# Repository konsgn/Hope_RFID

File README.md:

HOPE RFID reader.

By:Konstantin

Scans EM tags using a ATMEGA32u4.
Has usb for computer connection
Has nrf24l01+ section for wireless, 2 headers allow use of existing sparkfun breakout / HOPE 8 Badge.
Has 2-line LCD display
Has 2 LED's and buzzer tied to reader module.

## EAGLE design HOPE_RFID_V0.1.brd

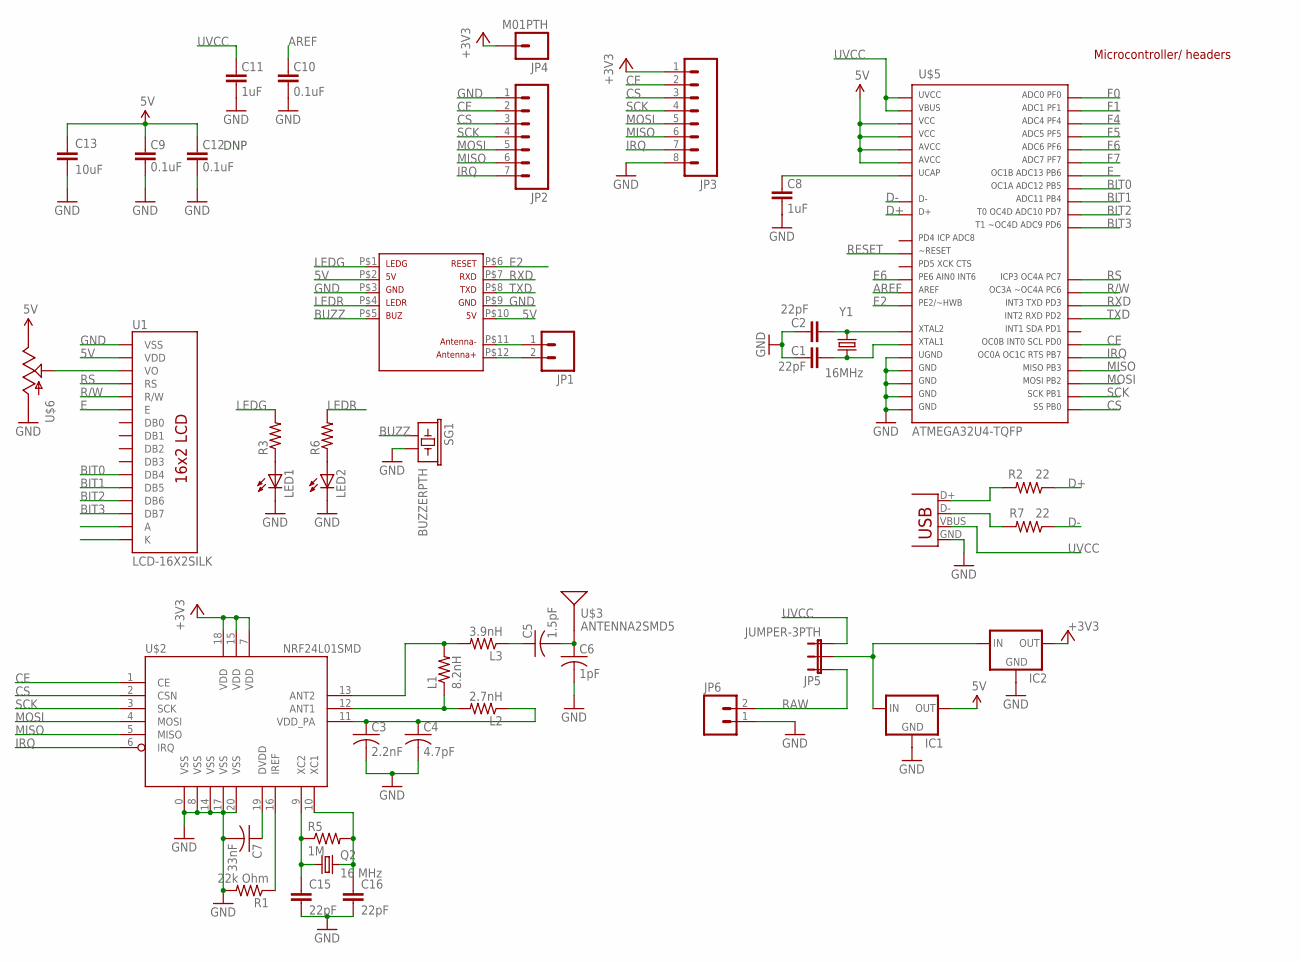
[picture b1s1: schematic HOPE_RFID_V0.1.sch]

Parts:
C1, C2: 22pF; 0805
C3: 2.2nF; C0402
C4: 4.7pF; C0402
C5: 1.5pF; C0402
C6: 1pF; C0402
C7: 33nF; C0402
C8, C11: 1uF; 0603-CAP
C9, C10, C12: 0.1uF; 0603-CAP
C13: 10uF; C2012
C15, C16: 22pF; 0603-CAP
IC1, IC2: V_REG_78XXSIDE; 78XXL
JP1: M02PTH; 1X02
JP2: M07; 1X07
JP3: M081X08; 1X08
JP4: M01PTH; 1X01
JP5: JUMPER-3PTH; 1X03
JP6: M023.5MM; SCREWTERMINAL-3.5MM-2
L1: 8.2nH; R0402
L2: 2.7nH; R0402
L3: 3.9nH; R0402
LED1, LED2: LED5MM
Q2: 16 MHz; CRYSTAL-SMD-5X3
R1: 22k Ohm; R0805
R2, R7: 22; 0805
R3, R6: RESISTORAXIAL-0.3; AXIAL-0.3
R5: 1M; R0805
SG1: BUZZERPTH; BUZZER-12MM
U1: LCD-16X2SILK; LCD-16X2
U$1: RDM880
U$2: NRF24L01SMD; QFN20
U$3: ANTENNA2SMD5; ANTENNA-CHIP5
U$5: ATMEGA32U4-TQFP; TQFP44
U$6: POTTRIM; TRIM_POT
X1: USB; USB-MINIB-NOHOLE
Y1: 16MHz; ABM2-8X4.5-CRYSTAL

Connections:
5V: C9.2, C12.2, C13.1, IC1.OUT, U1.2 (VDD), U$1.P$2, U$1.P$10, U$5.14, U$5.24, U$5.34, U$5.44, U$6.2 (E)
+3V3: IC2.OUT, JP3.1, JP4.1, U$2.7 (VDD), U$2.15 (VDD), U$2.18 (VDD)
AREF: C10.2, U$5.42
BIT0: U1.11 (DB4), U$5.29
BIT1: U1.12 (DB5), U$5.28
BIT2: U1.13 (DB6), U$5.27
BIT3: U1.14 (DB7), U$5.26
BUZZ: SG1.+ (1), U$1.P$5
CE: JP2.2, JP3.2, U$2.1 (CE), U$5.18
CS: JP2.3, JP3.3, U$2.2 (CSN), U$5.8
D+: R2.1, U$5.4
D-: R7.1, U$5.3
E: U1.6 (E), U$5.30
E2: U$1.P$6, U$5.33
E6: U$5.1
F0: U$5.41
F1: U$5.40
F4: U$5.39
F5: U$5.38
F6: U$5.37
F7: U$5.36
GND: C1.2, C2.2, C3.2, C4.2, C6.2, C7.2, C8.1, C9.1, C10.1, C11.1, C12.1, C13.2, C15.2, C16.2, IC1.GND, IC2.GND, JP2.1, JP3.8, JP6.1, LED1.K (C), LED2.K (C), R1.2, SG1.- (2), U1.1 (VSS), U$1.P$3, U$1.P$9, U$2.0 (VSS), U$2.8 (VSS), U$2.14 (VSS), U$2.17 (VSS), U$2.20 (VSS), U$5.5, U$5.15, U$5.23, U$5.35, U$5.43, U$6.3 (A), X1.GND
IRQ: JP2.7, JP3.7, U$2.6 (IRQ), U$5.12
LEDG: R3.P$2 (2), U$1.P$1
LEDR: R6.P$2 (2), U$1.P$4
MISO: JP2.6, JP3.6, U$2.5 (MISO), U$5.11
MOSI: JP2.5, JP3.5, U$2.4 (MOSI), U$5.10
unnamed: JP1.1, U$1.P$11
unnamed: JP1.2, U$1.P$12
unnamed: C15.1, Q2.1, R5.1, U$2.9 (XC2)
unnamed: C1.1, U$5.16, Y1.P$1 (1)
unnamed: C3.1, C4.1, L2.1, U$2.11 (VDD_PA)
unnamed: L1.1, L2.2, U$2.12 (ANT1)
unnamed: L1.2, L3.2, U$2.13 (ANT2)
unnamed: C5.1, L3.1
unnamed: C5.2, C6.1, U$3.FEED
unnamed: C2.1, U$5.17, Y1.P$2 (2)
unnamed: IC1.IN, IC2.IN, JP5.2
unnamed: C7.1, U$2.19 (DVDD)
unnamed: R1.1, U$2.16 (IREF)
unnamed: C8.2, U$5.6
unnamed: R7.2, X1.D-
unnamed: R2.2, X1.D+
unnamed: LED1.A, R3.P$1 (1)
unnamed: LED2.A, R6.P$1 (1)
unnamed: U1.3 (VO), U$6.1 (S)
unnamed: C16.1, Q2.3 (2), R5.2, U$2.10 (XC1)
R/W: U1.5 (R/W), U$5.31
RAW: JP5.1, JP6.2
RESET: U$5.13
RS: U1.4 (RS), U$5.32
RXD: U$1.P$7, U$5.21
SCK: JP2.4, JP3.4, U$2.3 (SCK), U$5.9
TXD: U$1.P$8, U$5.20
UVCC: C11.2, JP5.3, U$5.2, U$5.7, X1.VBUS

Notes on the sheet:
Microcontroller/ headers
DNP

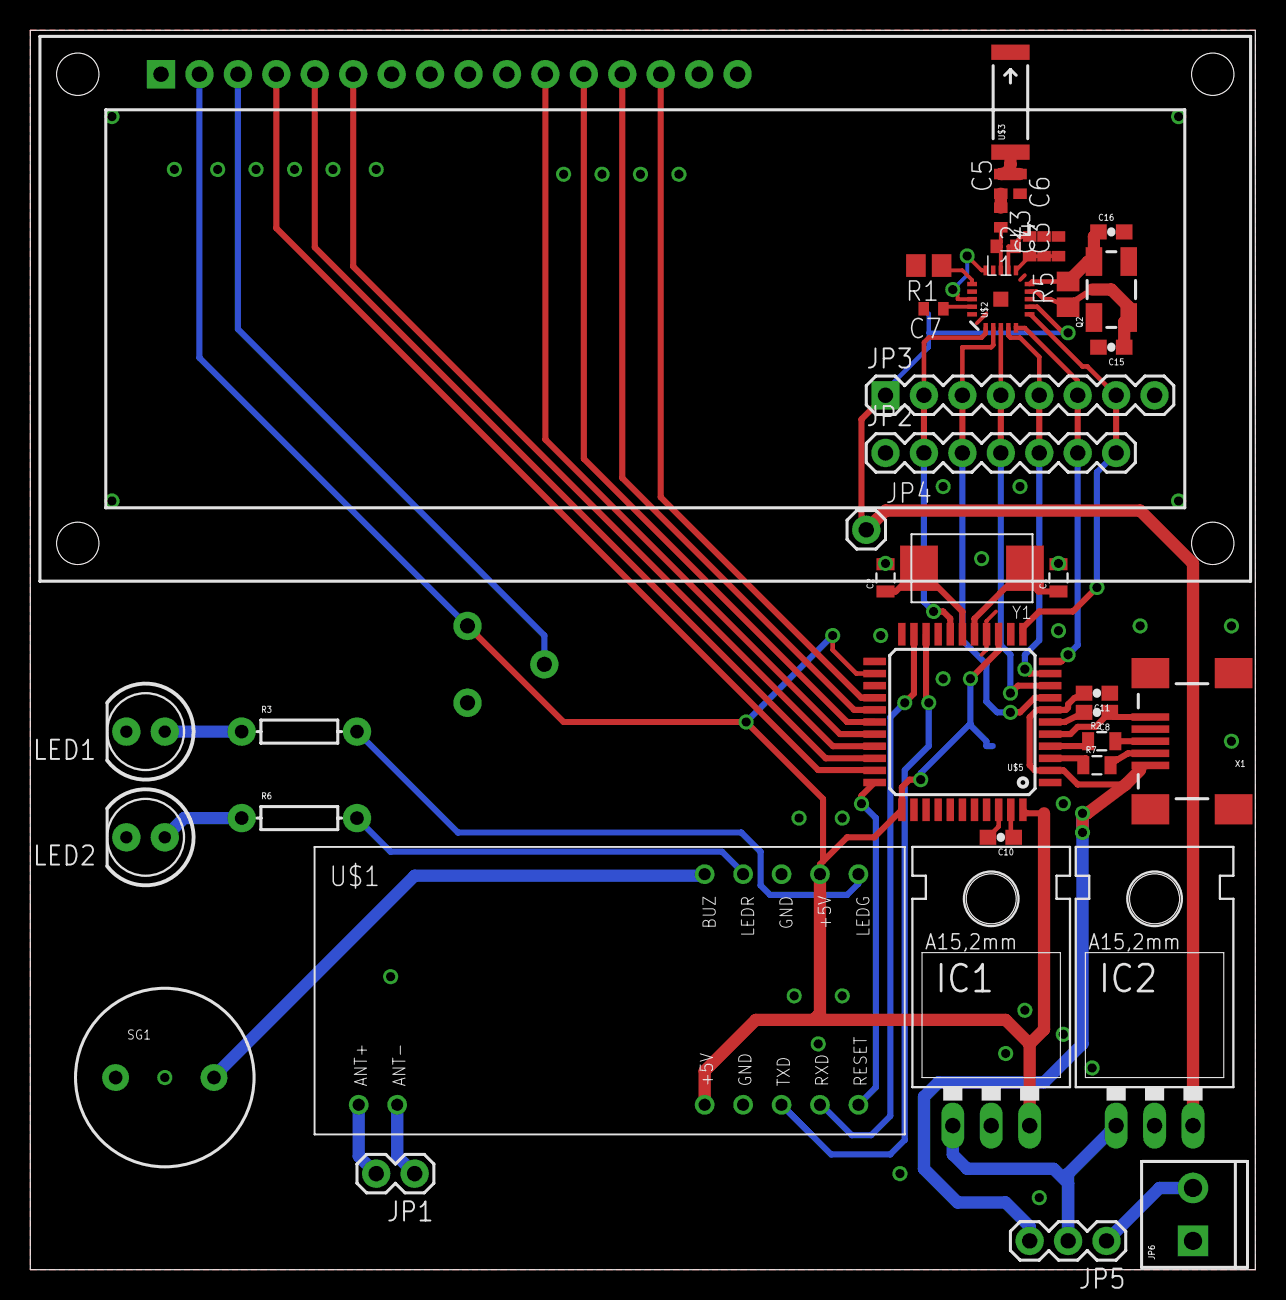
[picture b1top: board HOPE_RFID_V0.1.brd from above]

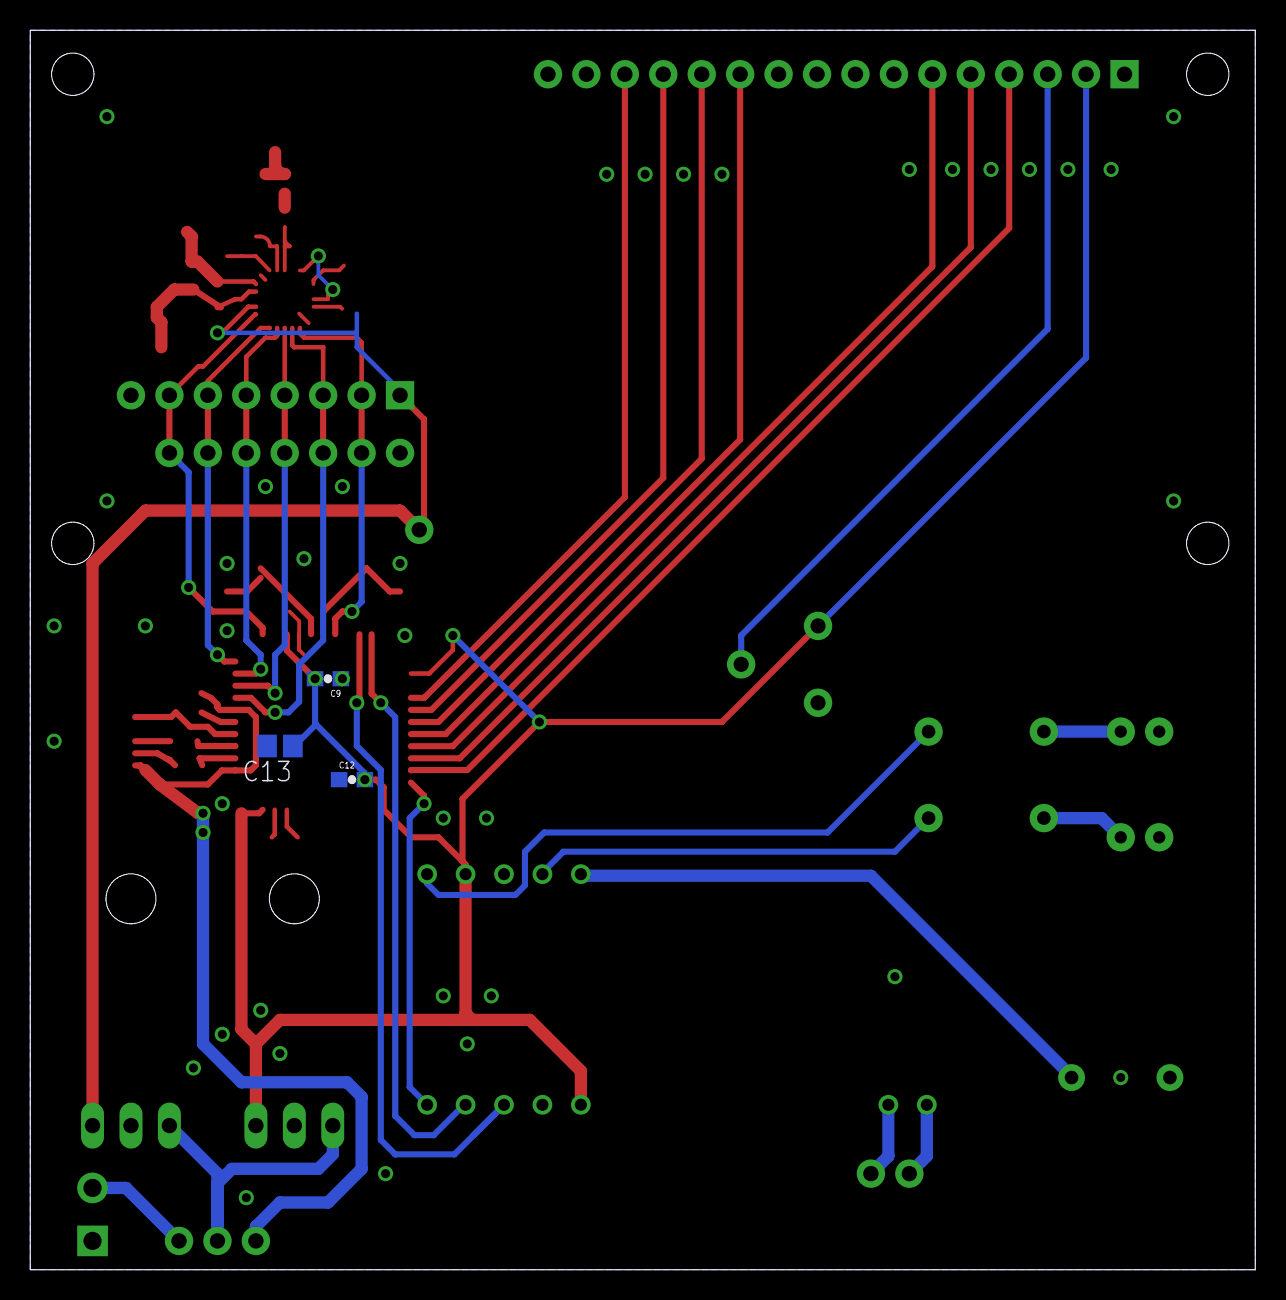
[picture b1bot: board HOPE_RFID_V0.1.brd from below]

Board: 2 copper layers, 81.0 x 81.9 mm, 44 parts (3 on the bottom side), 47 nets.
